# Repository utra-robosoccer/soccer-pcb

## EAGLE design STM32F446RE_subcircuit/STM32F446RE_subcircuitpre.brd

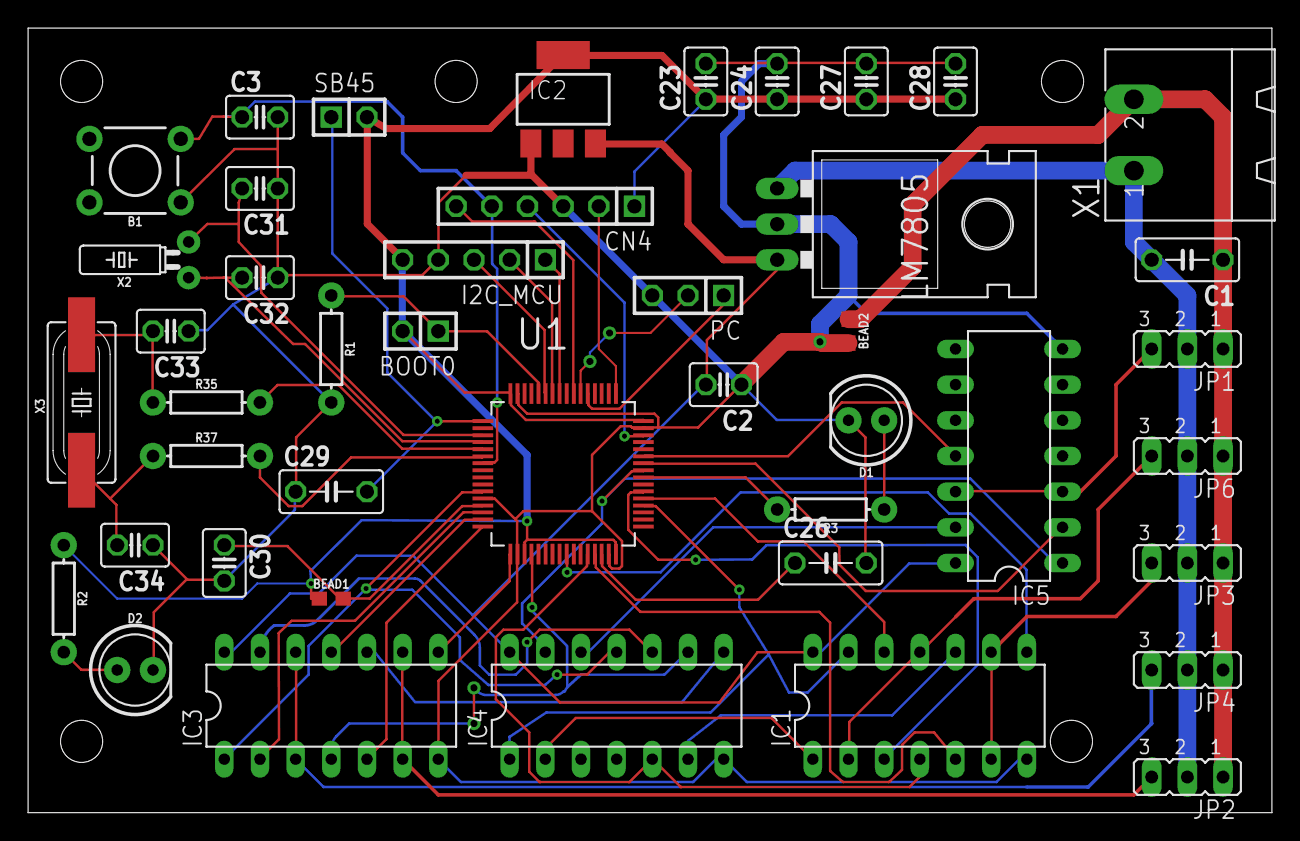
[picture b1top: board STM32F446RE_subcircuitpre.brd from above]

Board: 2 copper layers, 88.6 x 55.9 mm, 44 parts (0 on the bottom side), 52 nets.

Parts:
B1: 6MM(momentary); TACTILE_SWITCH_PTH_6.0MM
BEAD1, BEAD2: 30Ω/1.8A; 0603
BOOT0: 1X02
C1, C29: 1uF; C050-030-075
C2, C3, C23, C24, C27, C28, C30: 100nF; C025-030X050
C26: 4.7uF; C050-030-075
C31, C32: 4.3pF; C025-030X050
C33, C34: 20pF; C025-030X050
CN4: 1X06
D1, D2: LED_5MM
I2C_MCU: 1X05
IC1, IC3, IC5: 74AC126N; DIL14
IC2: LD117AS33TR; SOT223
IC4: 74HC04N; DIL14
JP1, JP2, JP3, JP4, JP6: JP2
LM7805: TO-220-ALT
PC: 1X03
R1: 10k; AXIAL-0.3
R2, R3, R35, R37: 1k; AXIAL-0.3
SB45: 1X02
U1: STM32F446RE; QFP50P1200X1200X160-64N
X1: MSTBA2
X2: 32.768kHz; CRYSTAL-PTH-2X6-CYL
X3: 8MHz; HC49UP

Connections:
5V: C2.2, IC1.14, IC2.3, IC3.14, IC4.14, IC5.14, LM7805.OUT
12V: C1.2, JP1.2, JP2.2, JP3.2, JP4.2, JP6.2, LM7805.IN, X1.1
AVDD: BEAD1.2, C30.1, U1.13
BOOT0: BOOT0.1, R1.P$1, U1.60
GND: B1.1, BEAD2.2, C2.1, C3.2, C23.2, C24.2, C26.2, C27.2, C28.2, C29.1, C30.2, C31.1, C32.1, C33.1, C34.1, CN4.3, D1.K, D2.K, I2C_MCU.4, IC1.7, IC2.1, IC3.7, IC4.7, IC5.7, LM7805.GND, PC.3, R1.P$2, U1.12, U1.18, U1.31, U1.47, U1.63
I2C1_SCL: I2C_MCU.2, U1.58
I2C1_SDA: I2C_MCU.3, U1.59
INT: I2C_MCU.1, U1.57
MGND: BEAD2.1, C1.1, JP1.1, JP2.1, JP3.1, JP4.1, JP6.1, X1.2
unnamed: R35.P$2, U1.5
unnamed: R37.P$2, U1.6
unnamed: IC1.1, IC4.2
unnamed: C34.2, R37.P$1, X3.1
unnamed: C33.2, R35.P$1, X3.2
unnamed: IC1.10, IC4.6
unnamed: D2.A, R2.P$2
unnamed: C31.2, U1.3, X2.2
unnamed: C32.2, U1.4, X2.1
unnamed: R3.P$2, U1.40
unnamed: IC3.13, IC4.10
unnamed: D1.A, R3.P$1
unnamed: IC3.10, IC4.8
unnamed: IC4.12, IC5.13
unnamed: IC5.3, IC5.12, JP1.3
NRST: B1.3, C3.1, CN4.5, U1.7
OUT1: IC1.2, IC1.11, JP6.3
OUT2: IC3.3, IC3.12, JP4.3
OUT3: IC1.6, IC1.9, JP3.3
OUT4: IC3.6, IC3.9, JP2.3
SWO: CN4.6, U1.55
TCK: CN4.2, U1.49
TMS: CN4.4, U1.46
U1_DIR: IC4.13, IC5.1, U1.41
U2_DIR: IC3.4, IC4.9, U1.20
U3_DIR: IC1.4, IC4.5, U1.28
U4_DIR: IC3.1, IC4.11, U1.11
U6_DIR: IC1.13, IC4.1, U1.36
UART4_RX: IC3.11, U1.15
UART4_TX: IC3.2, U1.14
USART1_RX: IC5.11, U1.43
USART1_TX: IC5.2, U1.42
USART2_RX: IC3.8, U1.17
USART2_TX: IC3.5, U1.16
USART3_RX: IC1.8, U1.25
USART3_TX: IC1.5, U1.29
USART5_RX: PC.2, U1.54
USART5_TX: PC.1, U1.53
USART6_RX: IC1.3, U1.38
USART6_TX: IC1.12, U1.37
VBAT: C29.2, SB45.1, U1.1
VCAP_1: C26.1, U1.30
VDD: BEAD1.1, BOOT0.2, C23.1, C24.1, C27.1, C28.1, CN4.1, I2C_MCU.5, IC2.4, R2.P$1, SB45.2, U1.19, U1.32, U1.48, U1.64

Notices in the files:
parts and their libraries:
SparkFun-Switches: Licensing: Creative Commons ShareAlike 4.0 International - https://creativecommons.org/licenses/by-sa/4.0
